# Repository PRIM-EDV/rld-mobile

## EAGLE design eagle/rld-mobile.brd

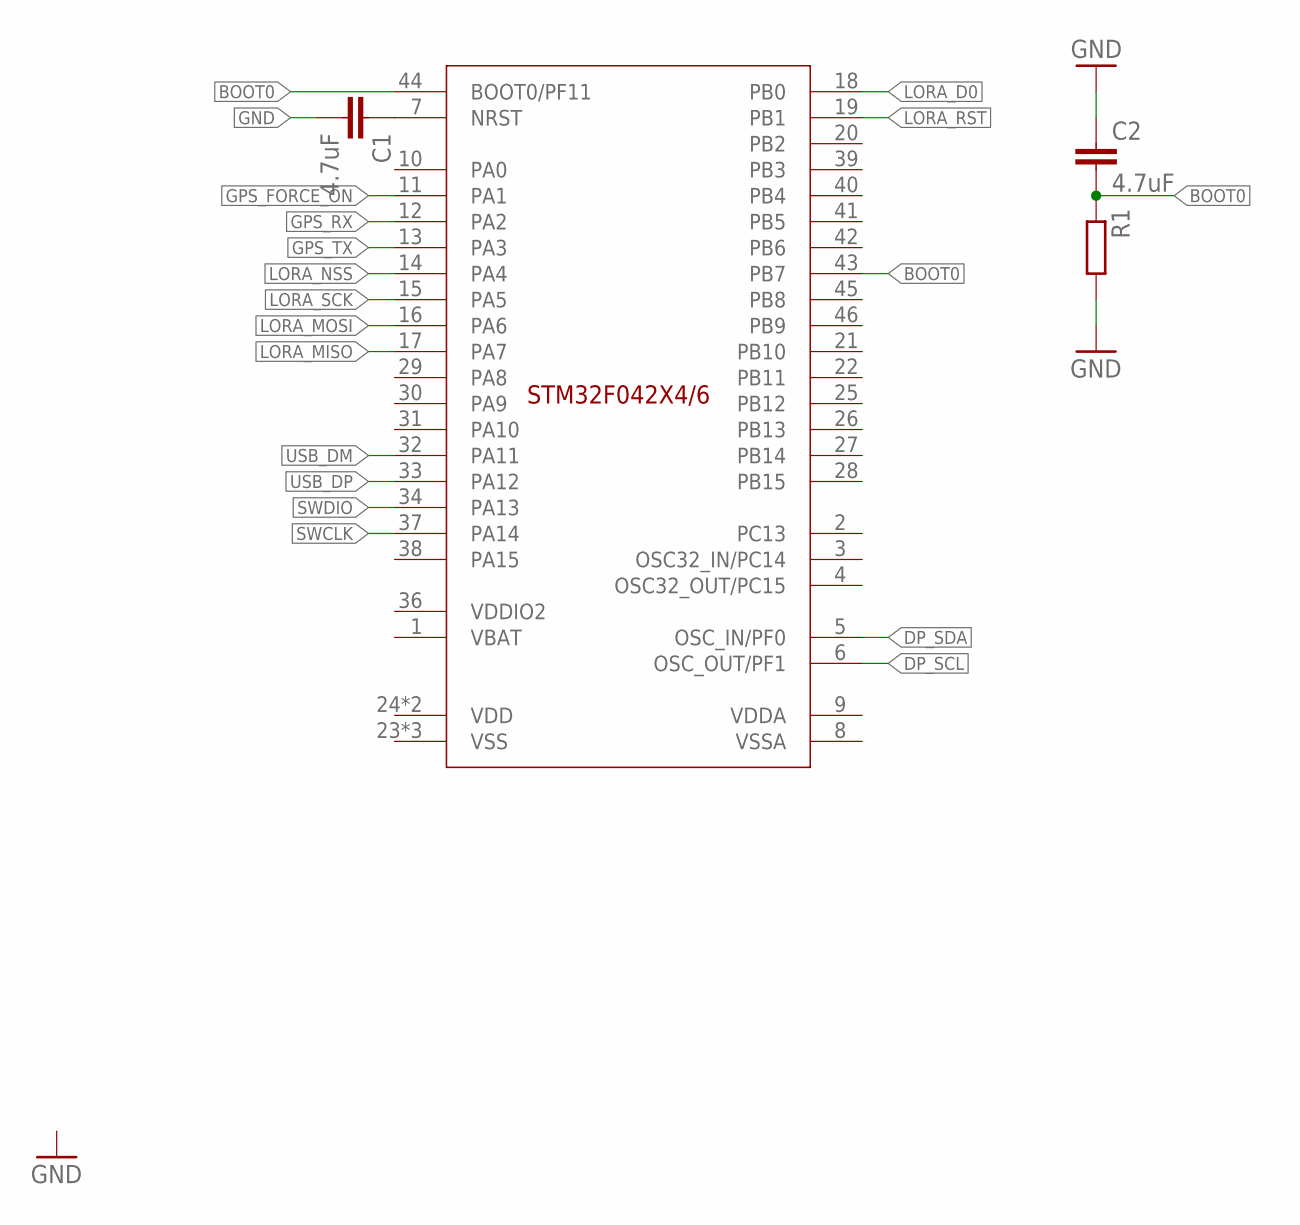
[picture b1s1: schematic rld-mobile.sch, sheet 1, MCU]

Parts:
C1, C2: 4.7uF; C0805
R1: R-EU_R0805; R0805
U$1: STM32-F042X4/6-48; UFQFPN48-7X7

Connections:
BOOT0: C2.2, R1.1, U$1.43 (PB7), U$1.44 (BOOT0/PF11)
DP_SCL: U$1.6 (OSC_OUT/PF1)
DP_SDA: U$1.5 (OSC_IN/PF0)
GND: C1.2, C2.1, R1.2
GPS_FORCE_ON: U$1.11 (PA1)
GPS_RX: U$1.12 (PA2)
GPS_TX: U$1.13 (PA3)
LORA_D0: U$1.18 (PB0)
LORA_MISO: U$1.17 (PA7)
LORA_MOSI: U$1.16 (PA6)
LORA_NSS: U$1.14 (PA4)
LORA_RST: U$1.19 (PB1)
LORA_SCK: U$1.15 (PA5)
unnamed: C1.1, U$1.7 (NRST)
SWCLK: U$1.37 (PA14)
SWDIO: U$1.34 (PA13)
USB_DM: U$1.32 (PA11)
USB_DP: U$1.33 (PA12)

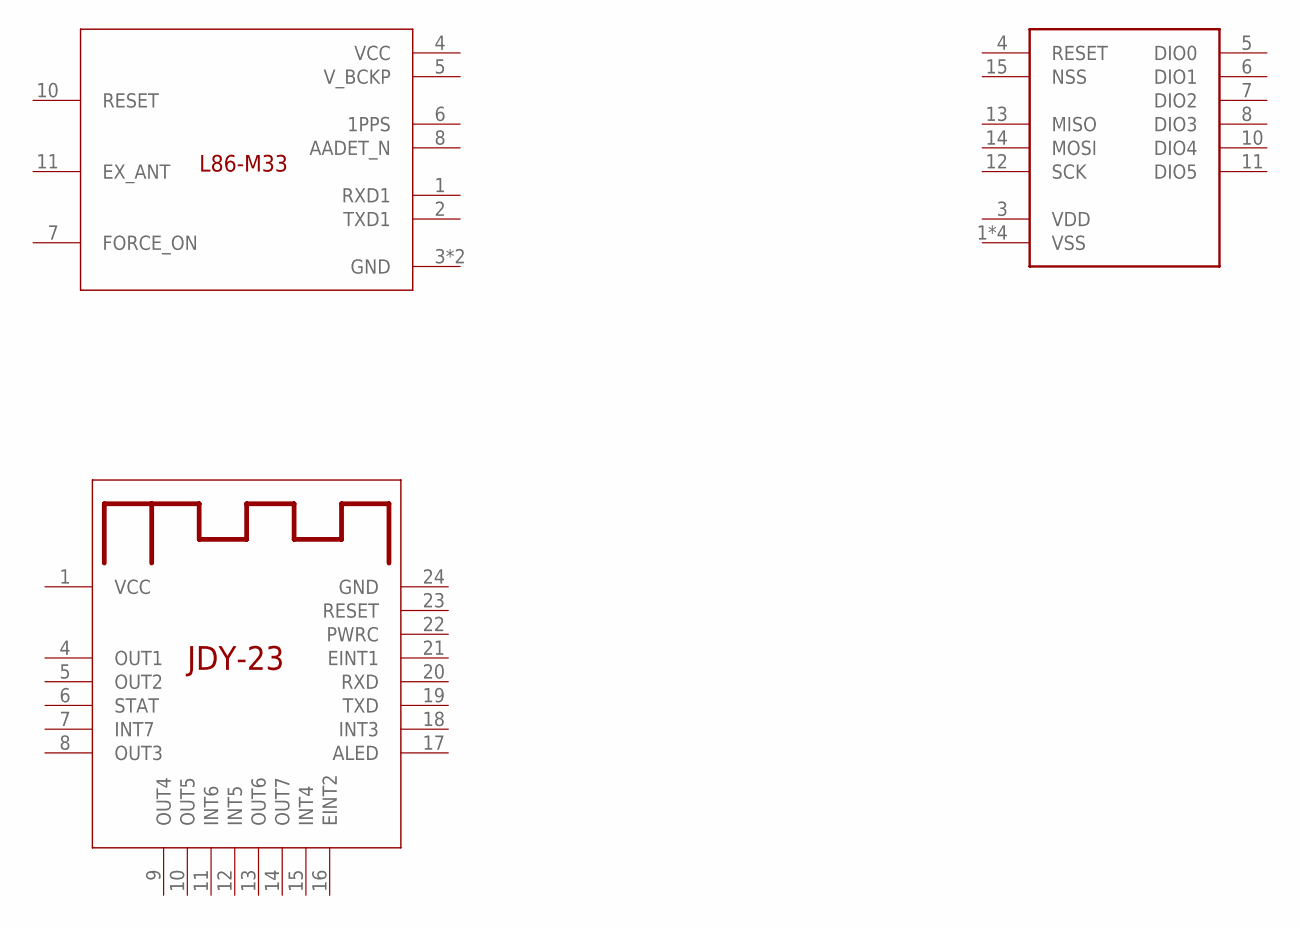
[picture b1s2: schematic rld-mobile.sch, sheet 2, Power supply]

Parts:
U$3: RA-02; RA-01/RA-02
U$4: L86-M33
U$5: JDY-23

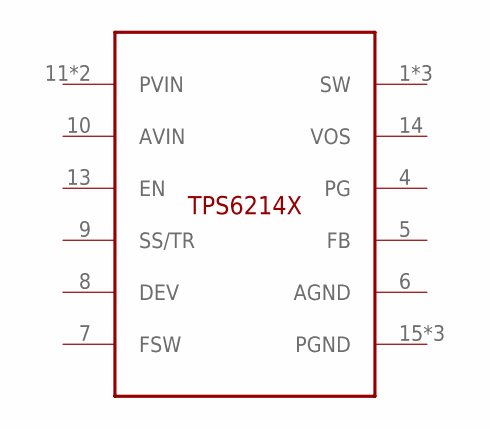
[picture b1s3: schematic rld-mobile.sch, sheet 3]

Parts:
U$2: TPS6214X; VQFN16-3X3

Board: 2 copper layers, 8 parts (0 on the bottom side), 3 nets, no tracks yet.

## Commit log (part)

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2019-02-01 pre-initial
    Prepared project for travis-ci
    Removed drawer icons
    Fixed wrong config for travis-ci
    Added android build tools to travis-ci config
    Fixed wrong config for travis-ci
    Prepared project for travis-ci
2019-04-14 Added rudimentary device features
2019-04-20 Upgraded to Ionic4
2019-05-07 Provided map as submodule
2019-05-07 Changed to prim repository.
2019-05-07 Fixed error in .gitmodules configuration
2019-05-09 Added configutation tab.
2019-05-09 Fix for node-sass error.
2019-05-14 Added wheel-menu boilerplate
2019-05-16 Added wheel-menu closing/opening
2019-05-20 Fixed issue with backend initialization
2019-05-30 Progressed configuration with tabbing
2019-08-11 Updated to Angular 8
2019-12-28 Bump handlebars from 4.1.2 to 4.5.3
    Bumps [handlebars](https://github.com/wycats/handlebars.js) from 4.1.2 to 4.5.3.
    - [Release notes](https://github.com/wycats/handlebars.js/releases)
    - [Changelog](https://github.com/wycats/handlebars.js/blob/master/release-notes.md)
    - [Commits](https://github.com/wycats/handlebars.js/compare/v4.1.2...v4.5.3)
2020-03-14 Bump acorn from 6.3.0 to 6.4.1
    Bumps [acorn](https://github.com/acornjs/acorn) from 6.3.0 to 6.4.1.
    - [Release notes](https://github.com/acornjs/acorn/releases)
    - [Commits](https://github.com/acornjs/acorn/compare/6.3.0...6.4.1)
2020-04-16 Bump https-proxy-agent from 2.2.2 to 2.2.4
    Bumps [https-proxy-agent](https://github.com/TooTallNate/node-https-proxy-agent) from 2.2.2 to 2.2.4.
    - [Release notes](https://github.com/TooTallNate/node-https-proxy-agent/releases)
    - [Commits](https://github.com/TooTallNate/node-https-proxy-agent/compare/2.2.2...2.2.4)
2020-07-07 Bump npm-registry-fetch from 4.0.0 to 4.0.5
    Bumps [npm-registry-fetch](https://github.com/npm/registry-fetch) from 4.0.0 to 4.0.5.
    - [Release notes](https://github.com/npm/registry-fetch/releases)
    - [Changelog](https://github.com/npm/npm-registry-fetch/blob/latest/CHANGELOG.md)
    - [Commits](https://github.com/npm/registry-fetch/commits)
2020-07-16 Bump lodash from 4.17.15 to 4.17.19
    Bumps [lodash](https://github.com/lodash/lodash) from 4.17.15 to 4.17.19.
    - [Release notes](https://github.com/lodash/lodash/releases)
    - [Commits](https://github.com/lodash/lodash/compare/4.17.15...4.17.19)
2020-09-04 Bump handlebars from 4.1.2 to 4.7.6
    Bumps [handlebars](https://github.com/wycats/handlebars.js) from 4.1.2 to 4.7.6.
    - [Release notes](https://github.com/wycats/handlebars.js/releases)
    - [Changelog](https://github.com/handlebars-lang/handlebars.js/blob/master/release-notes.md)
    - [Commits](https://github.com/wycats/handlebars.js/compare/v4.1.2...v4.7.6)
2020-09-08 Bump http-proxy from 1.17.0 to 1.18.1
    Bumps [http-proxy](https://github.com/http-party/node-http-proxy) from 1.17.0 to 1.18.1.
    - [Release notes](https://github.com/http-party/node-http-proxy/releases)
    - [Changelog](https://github.com/http-party/node-http-proxy/blob/master/CHANGELOG.md)
    - [Commits](https://github.com/http-party/node-http-proxy/compare/1.17.0...1.18.1)
2021-03-09 Bump elliptic from 6.5.0 to 6.5.4
    Bumps [elliptic](https://github.com/indutny/elliptic) from 6.5.0 to 6.5.4.
    - [Release notes](https://github.com/indutny/elliptic/releases)
    - [Commits](https://github.com/indutny/elliptic/compare/v6.5.0...v6.5.4)
2021-04-19 Bump ssri from 6.0.1 to 6.0.2
    Bumps [ssri](https://github.com/npm/ssri) from 6.0.1 to 6.0.2.
    - [Release notes](https://github.com/npm/ssri/releases)
    - [Changelog](https://github.com/npm/ssri/blob/v6.0.2/CHANGELOG.md)
    - [Commits](https://github.com/npm/ssri/compare/v6.0.1...v6.0.2)
2021-05-07 Bump handlebars from 4.1.2 to 4.7.7
    Bumps [handlebars](https://github.com/wycats/handlebars.js) from 4.1.2 to 4.7.7.
    - [Release notes](https://github.com/wycats/handlebars.js/releases)
    - [Changelog](https://github.com/handlebars-lang/handlebars.js/blob/master/release-notes.md)
    - [Commits](https://github.com/wycats/handlebars.js/compare/v4.1.2...v4.7.7)
2021-05-08 Bump lodash from 4.17.15 to 4.17.21
    Bumps [lodash](https://github.com/lodash/lodash) from 4.17.15 to 4.17.21.
    - [Release notes](https://github.com/lodash/lodash/releases)
    - [Commits](https://github.com/lodash/lodash/compare/4.17.15...4.17.21)
2021-05-09 Bump hosted-git-info from 2.8.4 to 2.8.9
    Bumps [hosted-git-info](https://github.com/npm/hosted-git-info) from 2.8.4 to 2.8.9.
    - [Release notes](https://github.com/npm/hosted-git-info/releases)
    - [Changelog](https://github.com/npm/hosted-git-info/blob/v2.8.9/CHANGELOG.md)
    - [Commits](https://github.com/npm/hosted-git-info/compare/v2.8.4...v2.8.9)
2021-05-27 Bump dns-packet from 1.3.1 to 1.3.4
    Bumps [dns-packet](https://github.com/mafintosh/dns-packet) from 1.3.1 to 1.3.4.
    - [Release notes](https://github.com/mafintosh/dns-packet/releases)
    - [Changelog](https://github.com/mafintosh/dns-packet/blob/master/CHANGELOG.md)
    - [Commits](https://github.com/mafintosh/dns-packet/compare/v1.3.1...v1.3.4)
2021-08-10 Bump path-parse from 1.0.6 to 1.0.7
    Bumps [path-parse](https://github.com/jbgutierrez/path-parse) from 1.0.6 to 1.0.7.
    - [Release notes](https://github.com/jbgutierrez/path-parse/releases)
    - [Commits](https://github.com/jbgutierrez/path-parse/commits/v1.0.7)
    ---
    updated-dependencies:
    - dependency-name: path-parse
2021-09-01 Bump tar from 4.4.8 to 4.4.19
    Bumps [tar](https://github.com/npm/node-tar) from 4.4.8 to 4.4.19.
    - [Release notes](https://github.com/npm/node-tar/releases)
    - [Changelog](https://github.com/npm/node-tar/blob/main/CHANGELOG.md)
    - [Commits](https://github.com/npm/node-tar/compare/v4.4.8...v4.4.19)
    ---
    updated-dependencies:
2021-10-05 Bump url-parse from 1.4.7 to 1.5.3
    Bumps [url-parse](https://github.com/unshiftio/url-parse) from 1.4.7 to 1.5.3.
    - [Release notes](https://github.com/unshiftio/url-parse/releases)
    - [Commits](https://github.com/unshiftio/url-parse/compare/1.4.7...1.5.3)
    ---
    updated-dependencies:
    - dependency-name: url-parse
2022-02-11 Bump karma from 3.1.4 to 6.3.14
    Bumps [karma](https://github.com/karma-runner/karma) from 3.1.4 to 6.3.14.
    - [Release notes](https://github.com/karma-runner/karma/releases)
    - [Changelog](https://github.com/karma-runner/karma/blob/master/CHANGELOG.md)
    - [Commits](https://github.com/karma-runner/karma/compare/v3.1.4...v6.3.14)
    ---
    updated-dependencies:
2022-02-12 Bump follow-redirects from 1.7.0 to 1.14.8
    Bumps [follow-redirects](https://github.com/follow-redirects/follow-redirects) from 1.7.0 to 1.14.8.
    - [Release notes](https://github.com/follow-redirects/follow-redirects/releases)
    - [Commits](https://github.com/follow-redirects/follow-redirects/compare/v1.7.0...v1.14.8)
    ---
    updated-dependencies:
    - dependency-name: follow-redirects
2022-02-26 Bump url-parse from 1.4.7 to 1.5.10
    Bumps [url-parse](https://github.com/unshiftio/url-parse) from 1.4.7 to 1.5.10.
    - [Release notes](https://github.com/unshiftio/url-parse/releases)
    - [Commits](https://github.com/unshiftio/url-parse/compare/1.4.7...1.5.10)
    ---
    updated-dependencies:
    - dependency-name: url-parse
2022-03-02 Bump karma from 3.1.4 to 6.3.16
    Bumps [karma](https://github.com/karma-runner/karma) from 3.1.4 to 6.3.16.
    - [Release notes](https://github.com/karma-runner/karma/releases)
    - [Changelog](https://github.com/karma-runner/karma/blob/master/CHANGELOG.md)
    - [Commits](https://github.com/karma-runner/karma/compare/v3.1.4...v6.3.16)
    ---
    updated-dependencies:
2022-04-13 Bump async from 2.6.3 to 3.2.2
    Bumps [async](https://github.com/caolan/async) from 2.6.3 to 3.2.2.
    - [Release notes](https://github.com/caolan/async/releases)
    - [Changelog](https://github.com/caolan/async/blob/master/CHANGELOG.md)
    - [Commits](https://github.com/caolan/async/compare/v2.6.3...v3.2.2)
    ---
    updated-dependencies:
2022-05-23 Expanded project structure
2022-06-01 Bump eventsource from 1.0.7 to 1.1.1
    Bumps [eventsource](https://github.com/EventSource/eventsource) from 1.0.7 to 1.1.1.
    - [Release notes](https://github.com/EventSource/eventsource/releases)
    - [Changelog](https://github.com/EventSource/eventsource/blob/master/HISTORY.md)
    - [Commits](https://github.com/EventSource/eventsource/compare/v1.0.7...v1.1.1)
    ---
    updated-dependencies:
2022-07-20 Bump terser from 4.1.4 to 4.8.1
    Bumps [terser](https://github.com/terser/terser) from 4.1.4 to 4.8.1.
    - [Release notes](https://github.com/terser/terser/releases)
    - [Changelog](https://github.com/terser/terser/blob/master/CHANGELOG.md)
    - [Commits](https://github.com/terser/terser/commits)
    ---
    updated-dependencies:
2022-09-08 Bump jszip from 3.2.2 to 3.10.1
    Bumps [jszip](https://github.com/Stuk/jszip) from 3.2.2 to 3.10.1.
    - [Release notes](https://github.com/Stuk/jszip/releases)
    - [Changelog](https://github.com/Stuk/jszip/blob/main/CHANGES.md)
    - [Commits](https://github.com/Stuk/jszip/compare/v3.2.2...v3.10.1)
    ---
    updated-dependencies:
2022-10-29 Bump socket.io-parser and karma
    Bumps [socket.io-parser](https://github.com/socketio/socket.io-parser) to 4.2.1 and updates ancestor dependency [karma](https://github.com/karma-runner/karma). These dependencies need to be updated t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
    Updates `socket.io-parser` from 3.2.0 to 4.2.1
    - [Release notes](https://github.com/socketio/socket.io-parser/releases)
    - [Changelog](https://github.com/socketio/socket.io-parser/blob/main/CHANGELOG.md)
    - [Commits](https://github.com/socketio/socket.io-parser/compare/3.2.0...4.2.1)
    Updates `karma` from 3.1.4 to 6.4.1
2022-11-22 Bump engine.io and karma
    Bumps [engine.io](https://github.com/socketio/engine.io) to 6.2.1 and updates ancestor dependency [karma](https://github.com/karma-runner/karma). These dependencies need to be updated together.
    Updates `engine.io` from 3.2.1 to 6.2.1
    - [Release notes](https://github.com/socketio/engine.io/releases)
    - [Changelog](https://github.com/socketio/engine.io/blob/main/CHANGELOG.md)
    - [Commits](https://github.com/socketio/engine.io/compare/3.2.1...6.2.1)
    Updates `karma` from 3.1.4 to 6.4.1
2022-12-02 Bump decode-uri-component from 0.2.0 to 0.2.2
    Bumps [decode-uri-component](https://github.com/SamVerschueren/decode-uri-component) from 0.2.0 to 0.2.2.
    - [Release notes](https://github.com/SamVerschueren/decode-uri-component/releases)
    - [Commits](https://github.com/SamVerschueren/decode-uri-component/compare/v0.2.0...v0.2.2)
    ---
    updated-dependencies:
    - dependency-name: decode-uri-component
2022-12-10 Bump express and cordova-browser
    Bumps [express](https://github.com/expressjs/express) to 4.18.2 and updates ancestor dependency [cordova-browser](https://github.com/apache/cordova-browser). These dependencies need to be updated tog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
    Updates `express` from 4.17.1 to 4.18.2
    - [Release notes](https://github.com/expressjs/express/releases)
    - [Changelog](https://github.com/expressjs/express/blob/master/History.md)
    - [Commits](https://github.com/expressjs/express/compare/4.17.1...4.18.2)
    Updates `cordova-browser` from 5.0.4 to 6.0.0
2023-01-01 Bump json5 and @angular-devkit/build-angular
    Bumps [json5](https://github.com/json5/json5) to 2.2.3 and updates ancestor dependency [@angular-devkit/build-angular](https://github.com/angular/angular-cli). These dependencies need to be updated t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
    Updates `json5` from 1.0.1 to 2.2.3
    - [Release notes](https://github.com/json5/json5/releases)
    - [Changelog](https://github.com/json5/json5/blob/main/CHANGELOG.md)
    - [Commits](https://github.com/json5/json5/compare/v1.0.1...v2.2.3)
    Updates `@angular-devkit/build-angular` from 0.801.3 to 15.0.4
